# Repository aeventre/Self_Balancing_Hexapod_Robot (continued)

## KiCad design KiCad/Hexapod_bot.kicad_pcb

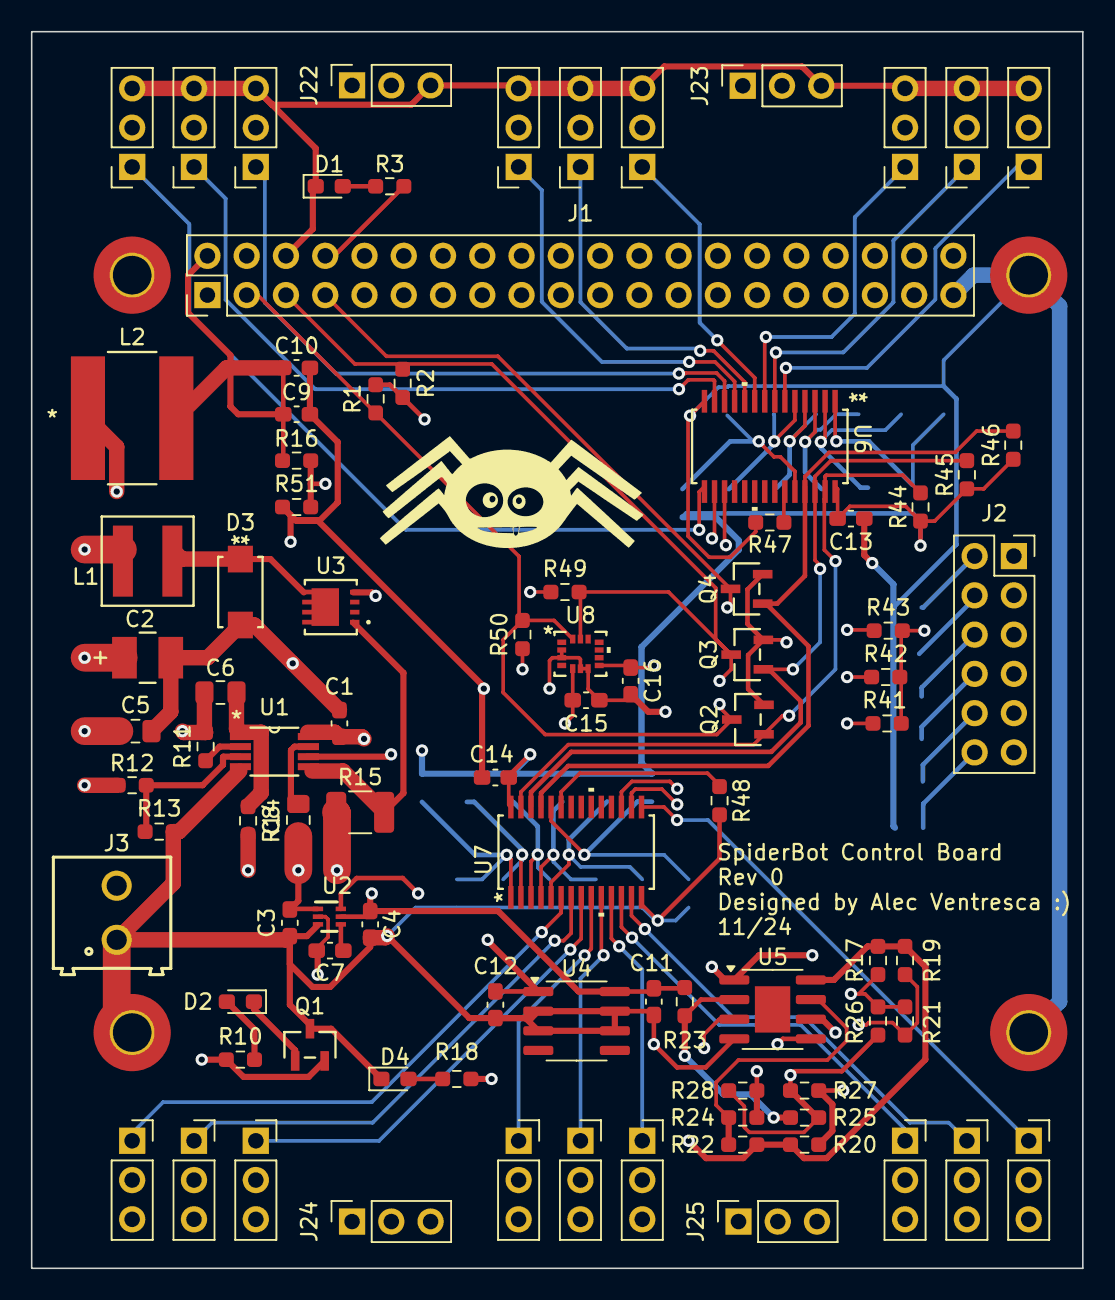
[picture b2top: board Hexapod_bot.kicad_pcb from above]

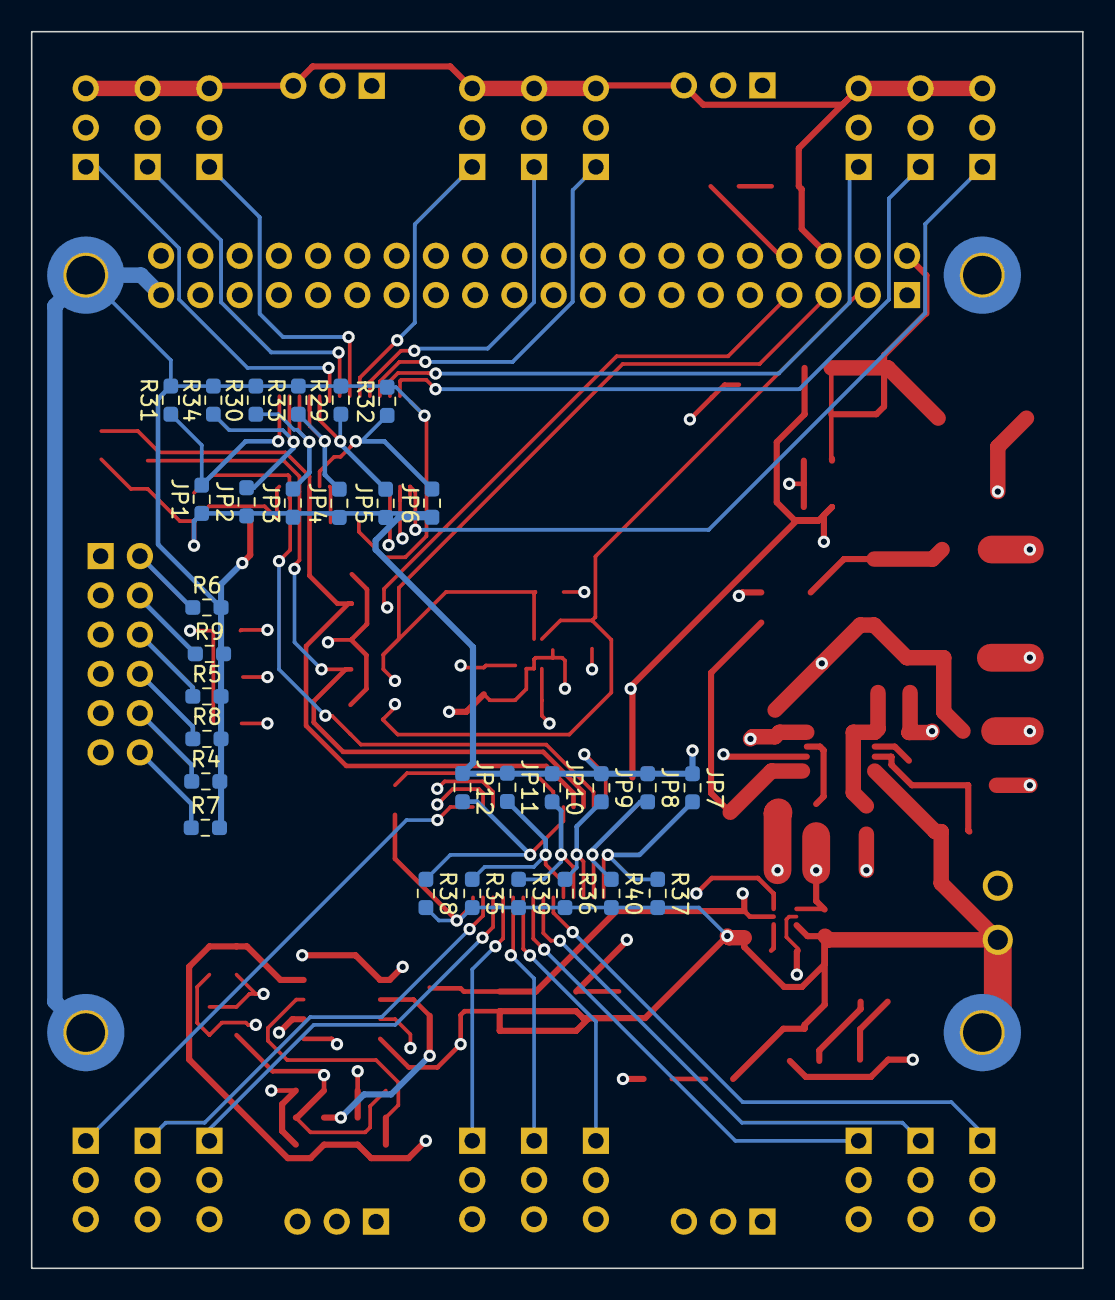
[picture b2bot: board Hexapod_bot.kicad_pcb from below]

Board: 4 copper layers, 68.0 x 80.0 mm, 126 parts (30 on the bottom side), 75 nets.

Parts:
C1, C9: 22uF; C_0603_1608Metric_Pad1.08x0.95mm_HandSolder
C2: 33uF; PCAP_TPB_B2_PAN
C3, C13, C14: 10uF; C_0603_1608Metric_Pad1.08x0.95mm_HandSolder
C4, C7, C10, C15, C16: 0.1uF; C_0603_1608Metric_Pad1.08x0.95mm_HandSolder
C5: 2.7nF; C_0805_2012Metric_Pad1.18x1.45mm_HandSolder
C6: 1nF; C_0805_2012Metric_Pad1.18x1.45mm_HandSolder
C8: 470nF; C_0805_2012Metric_Pad1.18x1.45mm_HandSolder
C11, C12: 0.1F; C_0603_1608Metric_Pad1.08x0.95mm_HandSolder
D1: LED Blue; LED_0603_1608Metric_Pad1.05x0.95mm_HandSolder
D2: Green LED; LED_0603_1608Metric_Pad1.05x0.95mm_HandSolder
D3: D_Schottky; DIODE_SODB340_2P92X4P6_DIO
D4: LED Red; LED_0603_1608Metric_Pad1.05x0.95mm_HandSolder
H1, H2, H3, H4: MountingHole_Pad; MountingHole_2.5mm_Pad_TopBottom
J1: Ras Pi 4 Interface; PinSocket_2x20_P2.54mm_Vertical
J2: Leg Switches; PinSocket_2x06_P2.54mm_Vertical
J3: Terminal Block; Terminal
J4, J5, J6, J7, J8, J9, J10, J11, J12, J13, J14, J15, J16, J17, J18, J19, J20, J21, J22, J23, J24, J25: Conn_01x03; PinSocket_1x03_P2.54mm_Vertical
JP1, JP2, JP3, JP4, JP5, JP6, JP7, JP8, JP9, JP10, JP11, JP12: SolderJumper_2_Open; R_0603_1608Metric_Pad0.98x0.95mm_HandSolder
L1: 600nH; IND_SRP5030CA_BRN
L2: 3.3uH; IND_BOURNS_SRN8040
Q1, Q2, Q3, Q4: BSS138; SOT-23_3L_ONS
R1, R2, R4, R5, R6, R7, R8, R9, R12, R19, R20, R22, R27, R29, R30, R31, R32, R33, R34, R35, R36, R37, R38, R39, R40, R41, R42, R43, R44, R45, R46, R47, R48, R49, R50, R51: 10k; R_0603_1608Metric_Pad0.98x0.95mm_HandSolder
R3: 1.2k; R_0603_1608Metric_Pad0.98x0.95mm_HandSolder
R10: 2.1k; R_0603_1608Metric_Pad0.98x0.95mm_HandSolder
R11: 56.2k; R_0603_1608Metric_Pad0.98x0.95mm_HandSolder
R13: 2.64k; R_0603_1608Metric_Pad0.98x0.95mm_HandSolder
R14: 4.12k; R_0603_1608Metric_Pad0.98x0.95mm_HandSolder
R15: 10m; R_1210_3225Metric_Pad1.30x2.65mm_HandSolder
R16: 73.2k; R_0603_1608Metric_Pad0.98x0.95mm_HandSolder
R17: 51k; R_0603_1608Metric_Pad0.98x0.95mm_HandSolder
R18: 1.6k; R_0603_1608Metric_Pad0.98x0.95mm_HandSolder
R21: 750k; R_0603_1608Metric_Pad0.98x0.95mm_HandSolder
R23: 82k; R_0603_1608Metric_Pad0.98x0.95mm_HandSolder
R24: 1k; R_0603_1608Metric_Pad0.98x0.95mm_HandSolder
R25: 27k; R_0603_1608Metric_Pad0.98x0.95mm_HandSolder
R26: 30k; R_0603_1608Metric_Pad0.98x0.95mm_HandSolder
R28: 2k; R_0603_1608Metric_Pad0.98x0.95mm_HandSolder
U1: LM25085MM/NOPB; MUA08A
U2: TPS563231DRLR; DRL0006A
U3: CSD25402Q3A
U4: LM78L05_SO8; SOIC-8_3.9x4.9mm_P1.27mm
U5: LM393; SOIC-8-1EP_3.9x4.9mm_P1.27mm_EP2.29x3mm
U6, U7: PCA9685PW; SOT361-1_NXP
U8: LSM6DSO32TR; LGA-14L_2P5X3X0P83_STM

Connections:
3V3_pi: C15.1, C16.1, J1.1, J2.1, J2.3, J2.5, J2.7, J2.9, J2.11, Q2.2 (G), Q3.2 (G), Q4.2 (G), R1.1, R2.1, R41.1, R42.1, R43.1, R49.1, R50.1, U8.5 (VDDIO), U8.8 (VDD)
5V_pi: C9.1, C10.1, C13.1, C14.1, J1.2, J22.2, J23.2, J24.2, J25.2, JP1.1 (A), JP2.1 (A), JP3.1 (A), JP4.1 (A), JP5.1 (A), JP6.1 (A), JP7.1 (A), JP8.1 (A), JP9.1 (A), JP10.1 (A), JP11.1 (A), JP12.1 (A), L2.2, R16.1, R44.1, R45.1, R46.1, U6.28 (VDD), U7.28 (VDD)
6V_servo: C2.1, C5.1, J4.2, J5.2, J6.2, J7.2, J8.2, J9.2, J10.2, J11.2, J12.2, J13.2, J14.2, J15.2, J16.2, J17.2, J18.2, J19.2, J20.2, J21.2, L1.1, Q1.2 (G), R10.1, R12.1
7.4V_batt: C1.1, C3.1, C4.1, C6.1, C8.1, C11.1, J3.2, R11.2, R14.1, R15.1, R23.1, U1.8 (VIN), U2.1 (VIN), U2.5 (EN), U4.8 (IN)
/servo_control/A5_1: JP6.2 (B), R32.1, U6.24 (A5)
/servo_control/A5_2: JP12.2 (B), R38.1, U7.24 (A5)
/servo_control/CLK_5V: Q4.1 (D), R46.2, U6.25 (EXTCLK), U7.25 (EXTCLK)
/servo_control/SCL_5V: Q3.1 (D), R45.2, U6.26 (SCL), U7.26 (SCL)
/servo_control/SDA_5V: Q2.1 (D), R44.2, U6.27 (SDA), U7.27 (SDA)
/servo_control/pwm1: J22.1, U6.16 (LED9)
/servo_control/pwm2: J23.1, U6.17 (LED10)
/servo_control/pwm3: J24.1, U7.16 (LED9)
/servo_control/pwm4: J25.1, U7.17 (LED10)
/servo_control/servo0: J12.1, U6.6 (LED0)
/servo_control/servo1: J11.1, U6.7 (LED1)
/servo_control/servo2: J10.1, U6.8 (LED2)
/servo_control/servo3: J9.1, U6.9 (LED3)
/servo_control/servo4: J8.1, U6.10 (LED4)
/servo_control/servo5: J7.1, U6.11 (LED5)
/servo_control/servo6: J6.1, U6.12 (LED6)
/servo_control/servo7: J5.1, U6.13 (LED7)
/servo_control/servo8: J4.1, U6.15 (LED8)
/servo_control/servo9: J13.1, U7.6 (LED0)
/servo_control/servo10: J14.1, U7.7 (LED1)
/servo_control/servo11: J15.1, U7.8 (LED2)
/servo_control/servo12: J16.1, U7.9 (LED3)
/servo_control/servo13: J17.1, U7.10 (LED4)
/servo_control/servo14: J18.1, U7.11 (LED5)
/servo_control/servo15: J19.1, U7.12 (LED6)
/servo_control/servo16: J20.1, U7.13 (LED7)
/servo_control/servo17: J21.1, U7.15 (LED8)
BattLow: J1.13, R24.2, R28.2
CLK_3V3: J1.7, Q4.3 (S), R43.2
GND: C1.2, C2.2, C3.2, C4.2, C5.2, C9.2, C10.2, C11.2, C12.2, C13.2, C14.2, C15.2, C16.2, D1.1 (K), D3.2 (A), D4.1 (K), H1.1, H2.1, H3.1, H4.1, J1.6, J1.39, J3.1, J4.3, J5.3, J6.3, J7.3, J8.3, J9.3, J10.3, J11.3, J12.3, J13.3, J14.3, J15.3, J16.3, J17.3, J18.3, J19.3, J20.3, J21.3, J22.3, J23.3, J24.3, J25.3, Q1.3 (S), R4.2, R5.2, R6.2, R7.2, R8.2, R9.2, R13.2, R25.2, R26.2, R27.2, R28.1, R29.2, R30.2, R31.2, R32.2, R33.2, R34.2, R35.2, R36.2, R37.2, R38.2, R39.2, R40.2, R47.2, R48.2, R51.2, U1.4 (GND), U2.3 (GND), U4.2 (GND), U4.3 (GND), U4.6 (GND), U4.7 (GND), U5.4 (V-), U6.14 (VSS), U7.14 (VSS), U8.2 (SDx), U8.3 (SCx), U8.6 (GND), U8.7 (GND)
unnamed: D1.2 (A), R3.1
unnamed: D2.2 (A), R10.2
unnamed: D2.1 (K), Q1.1 (D)
unnamed: D3.1 (K), L1.2, U3.5 (S), U3.6 (S), U3.7 (S), U3.8 (S), U3.9 (S)
unnamed: D4.2 (A), R18.2
unnamed: J1.8, R3.2
unnamed: J1.27, J2.2, R6.1
unnamed: J1.29, J2.4, R9.1
unnamed: J1.31, J2.6, R5.1
unnamed: J1.33, J2.8, R8.1
unnamed: J1.35, J2.10, R4.1
unnamed: J1.37, J2.12, R7.1
unnamed: JP1.2 (B), R31.1, U6.1 (A0)
unnamed: JP2.2 (B), R34.1, U6.2 (A1)
unnamed: JP3.2 (B), R30.1, U6.3 (A2)
unnamed: JP4.2 (B), R33.1, U6.4 (A3)
unnamed: JP5.2 (B), R29.1, U6.5 (A4)
unnamed: JP7.2 (B), R37.1, U7.1 (A0)
unnamed: JP8.2 (B), R40.1, U7.2 (A1)
unnamed: JP9.2 (B), R36.1, U7.3 (A2)
unnamed: JP10.2 (B), R39.1, U7.4 (A3)
unnamed: JP11.2 (B), R35.1, U7.5 (A4)
unnamed: R22.2, R24.1, U5.7
unnamed: C6.2, R14.2, U1.1 (ADJ)
unnamed: R12.2, R13.1, U1.3 (FB)
unnamed: R15.2, U1.5 (ISEN), U3.1 (D), U3.2 (D), U3.3 (D)
unnamed: U1.6 (PGATE), U3.4 (G)
unnamed: R11.1, U1.2 (RT)
unnamed: C8.2, U1.7 (VCC)
unnamed: C7.1, U2.4 (CB)
unnamed: R16.2, R51.1, U2.6 (FB)
unnamed: C7.2, L2.1, U2.2 (SW)
unnamed: C12.1, R17.1, R19.1, R20.1, R22.1, U4.1 (OUT), U5.8 (V+)
unnamed: R17.2, R21.1, R26.1, U5.3 (+)
unnamed: R23.2, R25.1, U5.2 (-)
unnamed: R20.2, R27.1, U5.5 (+)
unnamed: R18.1, R19.2, R21.2, U5.1, U5.6 (-)
unnamed: R47.1, U6.23 (*OE)
unnamed: R48.1, U7.23 (*OE)
SCL_3V3: J1.5, Q3.3 (S), R2.2, R42.2, R49.2, U8.13 (SCL)
SDA_3V3: J1.3, Q2.3 (S), R1.2, R41.2, R50.2, U8.14 (SDA)

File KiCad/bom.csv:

"Reference","Value","Footprint","Qty"
"U8","LSM6DSO32TR","Spiderbot:LGA-14L_2P5X3X0P83_STM","1"
"U6,U7","PCA9685PW","Spiderbot:SOT361-1_NXP","2"
"U5","LM393","Package_SO:SOIC-8-1EP_3.9x4.9mm_P1.27mm_EP2.29x3mm","1"
"U4","LM78L05_SO8","Package_SO:SOIC-8_3.9x4.9mm_P1.27mm","1"
"U3","CSD25402Q3A","Spiderbot:CSD25402Q3A","1"
"U2","TPS563231DRLR","Spiderbot:DRL0006A","1"
"U1","LM25085MM/NOPB","Spiderbot:MUA08A","1"
"R28","2k","Resistor_SMD:R_0603_1608Metric_Pad0.98x0.95mm_HandSolder","1"
"R26","30k","Resistor_SMD:R_0603_1608Metric_Pad0.98x0.95mm_HandSolder","1"
"R25","27k","Resistor_SMD:R_0603_1608Metric_Pad0.98x0.95mm_HandSolder","1"
"R24","1k","Resistor_SMD:R_0603_1608Metric_Pad0.98x0.95mm_HandSolder","1"
"R23","82k","Resistor_SMD:R_0603_1608Metric_Pad0.98x0.95mm_HandSolder","1"
"R21","750k","Resistor_SMD:R_0603_1608Metric_Pad0.98x0.95mm_HandSolder","1"
"R18","1.6k","Resistor_SMD:R_0603_1608Metric_Pad0.98x0.95mm_HandSolder","1"
"R17","51k","Resistor_SMD:R_0603_1608Metric_Pad0.98x0.95mm_HandSolder","1"
"R16","73.2k","Resistor_SMD:R_0603_1608Metric_Pad0.98x0.95mm_HandSolder","1"
"R15","10m","Resistor_SMD:R_1210_3225Metric_Pad1.30x2.65mm_HandSolder","1"
"R14","4.12k","Resistor_SMD:R_0603_1608Metric_Pad0.98x0.95mm_HandSolder","1"
"R13","2.64k","Resistor_SMD:R_0603_1608Metric_Pad0.98x0.95mm_HandSolder","1"
"R11","56.2k","Resistor_SMD:R_0603_1608Metric_Pad0.98x0.95mm_HandSolder","1"
"R10","2.1k","Resistor_SMD:R_0603_1608Metric_Pad0.98x0.95mm_HandSolder","1"
"R3","1.2k","Resistor_SMD:R_0603_1608Metric_Pad0.98x0.95mm_HandSolder","1"
"R1,R2,R4,R5,R6,R7,R8,R9,R12,R19,R20,R22,R27,R29,R30,R31,R32,R33,R34,R35,R36,R37,R38,R39,R40,R41,R42,R43,R44,R45,R46,R47,R48,R49,R50,R51","10k","Resistor_SMD:R_0603_1608Metric_Pad0.98x0.95mm_HandSolder","36"
"Q1,Q2,Q3,Q4","BSS138","Spiderbot:SOT-23_3L_ONS","4"
"L2","3.3uH","Spiderbot:IND_BOURNS_SRN8040","1"
"L1","600nH","Spiderbot:IND_SRP5030CA_BRN","1"
"JP1,JP2,JP3,JP4,JP5,JP6,JP7,JP8,JP9,JP10,JP11,JP12","SolderJumper_2_Open","Resistor_SMD:R_0603_1608Metric_Pad0.98x0.95mm_HandSolder","12"
"J4,J5,J6,J7,J8,J9,J10,J11,J12,J13,J14,J15,J16,J17,J18,J19,J20,J21,J22,J23,J24,J25","Conn_01x03","Connector_PinSocket_2.54mm:PinSocket_1x03_P2.54mm_Vertical","22"
"J3","Terminal Block","Spiderbot:Terminal","1"
"J2","Leg Switches","Connector_PinSocket_2.54mm:PinSocket_2x06_P2.54mm_Vertical","1"
"J1","Ras Pi 4 Interface","Connector_PinSocket_2.54mm:PinSocket_2x20_P2.54mm_Vertical","1"
"D4","LED Red","LED_SMD:LED_0603_1608Metric_Pad1.05x0.95mm_HandSolder","1"
"D3","D_Schottky","Spiderbot:DIODE_SODB340_2P92X4P6_DIO","1"
"D2","Green LED","LED_SMD:LED_0603_1608Metric_Pad1.05x0.95mm_HandSolder","1"
"D1","LED Blue","LED_SMD:LED_0603_1608Metric_Pad1.05x0.95mm_HandSolder","1"
"C11,C12","0.1F","Capacitor_SMD:C_0603_1608Metric_Pad1.08x0.95mm_HandSolder","2"
"C8","470nF","Capacitor_SMD:C_0805_2012Metric_Pad1.18x1.45mm_HandSolder","1"
"C6","1nF","Capacitor_SMD:C_0805_2012Metric_Pad1.18x1.45mm_HandSolder","1"
"C5","2.7nF","Capacitor_SMD:C_0805_2012Metric_Pad1.18x1.45mm_HandSolder","1"
"C4,C7,C10,C15,C16","0.1uF","Capacitor_SMD:C_0603_1608Metric_Pad1.08x0.95mm_HandSolder","5"
"C3,C13,C14","10uF","Capacitor_SMD:C_0603_1608Metric_Pad1.08x0.95mm_HandSolder","3"
"C2","33uF","Spiderbot:PCAP_TPB_B2_PAN","1"
"C1,C9","22uF","Capacitor_SMD:C_0603_1608Metric_Pad1.08x0.95mm_HandSolder","2"

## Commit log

2024-11-08 Almost finished with schematic, just need battery low voltage detection
2024-11-08 Rearranged some files
2024-11-08 Added Gitignore
2024-11-12 Finished Rev 1 of the PCB
2024-11-14 Get rid of backups
2024-11-14 Moved Gitignore
2024-11-14 Created ros_ws folder for ROS2 packages and added gitignore
2024-11-14 Created ROS2 kinematics package
2024-11-14 created main
2024-11-15 Created bom
2024-11-16 Updated Readme with ROS2 tutorials
2024-11-21 Changed 6V power line schematic
2024-11-25 Finished first revision of the PCB
2024-11-25 edited GITIGNORE
2024-11-25 Created package for i2c communications with imu and servo controllers
2024-11-25 added gitignores
2024-11-26 added scripts for setting up the python virtual environment and added instructions to the README
2024-11-27 got rid of i2c_comms so it can be separated into separate pkgs
2024-11-27 Created the servo_control package as well as a launch script for launching it without the second PCA because it isn't working rn
2024-11-27 Created utilities node with a calibrate_servos script
2024-11-27 Remove build/install/log from tracking
2024-11-27 Created python package for reading off of imu
2024-11-27 Added code and launch file for this package
2024-11-27 Successfully got the package to read and publish the IMU data!
2024-11-29 Inverse Kinematics looking into a single leg to do the computational work and then the entire hexapod as a whole. Also uses a visualization code to see where the robots position is at that point in t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
2024-11-30 Adjusted PWM ranges to get full range of motion on the servos
2024-11-30 Saved calibration offsets which the controller reads. So we don't need to think about it
2024-11-30 Created support_polygon_calculator and moved the servo offsets into the servo control package
2024-11-30 Added library dependencies
2024-12-01 Added publisher and subscriber code to support_polygon_calculator
2024-12-01 I literally have no idea how this code works. I thought I knew c++
2024-12-01 Still have no idea what's happening, but gonna try testing it
2024-12-01 support_polygon_calculator package is debugged and fully functional!
2024-12-01 Create LICENSE
2024-12-01 Created package structure for CoM_calculator
2024-12-01 Made package a python c++ hybrid
2024-12-01 This package is currently a mess, needs some reorganizing
2024-12-01 Switched to a python package for simplicity
2024-12-01 Created package for custom messages, includes leg positions
2024-12-01 changed the inverse kinemtics code to subscribe to and publish data from the ros package
2024-12-01 Git is acting wierd
2024-12-01 Merged msgs branch into kinematics
2024-12-01 Added more custom topics to msgs package, and made a topic list in the readme
2024-12-01 fixed inverse kinematics node code to subscribe to the leg commands and created the launch file
2024-12-02 Updated for new topic list
2024-12-02 Node works, need to verify if the math is correct
2024-12-02 made changes to publish pose topic
2024-12-02 fixed some small spelling errors that were messing up my code! :(
2024-12-02 updated all of the kinematics code and it is now running but also is not and it is stupid and i am mad
2024-12-02 I'm gonna use a bunch of existing libraries for the kinematics so I made a working urdf
2024-12-02 Saying Fuck it We Ball and made a new python package!
2024-12-02 Created pose presets
2024-12-02 The inverse kinematics kinda works, forward dont :(
2024-12-02 added package.xml
2024-12-02 jduosndv
2024-12-02 readme
2024-12-06 Finished Rev2 of the PCB
2024-12-06 Added some labels to the schematic
2024-12-06 Added PDF of electrical schematics
2024-12-08 Update README.md
    Added the image of the ros packages schematic into the readme
2024-12-09 Update README.md
    updated the overview, key objectives, and future goals of the project
2024-12-09 Update README.md
    Added the kinematics and COM calculator readme information
2024-12-09 Rearrange PCB files into electronics folder and update README
2024-12-09 Moved files around
2024-12-09 Reverted Changes
2024-12-09 Update README.md
    fixed some grammatical issues and reworded the future ideas/plans to make it sound more professional
2024-12-09 Update README.md
    fixed a few grammatical errors
2024-12-10 Add gpio_sensors to the main branch
2025-01-20 Add robotics toolbox to requirements
2025-09-15 Backlink to CADLAB.io has been added.
